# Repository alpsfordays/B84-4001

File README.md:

# B84-4001

The B84-4001 keyboard PCB is a replacement (rejuvenation? revival?) PCB that makes use of the G84-4001's layout, switches, and keycaps and puts them into a subjectively more usable form. It was originally created as a personal project to make use of a new-old-stock controller-less G84 module (a G84-4001QAU/00).

It supports one layout, the 83-key layout used by the aforementioned modules, though support for G84 variants with Windows keys may be added in future. No promises. It's all autorouted too, which may change as I work on this more.

I will gladly assist or give tips on assembly, firmware or use (you can find me on Discord as `bean#7178`), but please first read this README through.

This board is designed for Cherry ML switches in 18mm spacing, mounted directly onto the PCB; ML does not use a plate to hold the switches. The PCB has M2 mount holes along the perimeter, allowing one to make it into a sandwich case with another PCB as the backplate or mount into a custom case. This is **will not fit** in Cherry G84 keyboard cases - it is meant as a standalone keyboard.

I ordered revision zero with green soldermask, 0.8 millimetre with HASL. Revision one (what this repo is) has had its edges tidied up and excess silkscreen reference markings removed. When ordering, I highly recommend *not* specifying 0.8mm thickness - the stock PCB is 1.6mm so I recommend that.

### Controller and Firmware

This board uses an [RP2040 ItsyBitsy](https://www.adafruit.com/product/4888) from Adafruit as the keyboard controller, and the firmware is written in [KMK](https://github.com/KMKfw/kmk_firmware). It should be compatible with any other ItsyBitsy, including the 32u4 variant, but I've yet to try any of those and there may be some tweaks to KMK needed to support them (and of course for the 32u4, a port to TMK/QMK).

### Assembly

Here's the order of operations.

1.  Assemble your parts.
	* 83 Cherry ML switches
	* 83 1N4148 diodes, through-hole or SMD
	* 2.56mm headers
	* An RP2040 ItsyBitsy
	* Keycaps
	* Stabilizer inserts
	* (for sandwich casing) M2\*8 standoffs and M2\*3 screws, rubber feet and a second PCB

2.  Solder the diodes
	* Cathode to the square pads.
	* You will notice there are two sides to the PCB, a side **with** silkscreen and a side without. The side **with** silkscreen is the side from which you will insert or place the diodes - although the pads are also on the other, silkscreen-less side, do not put the diodes on that side unless you wish to have your keycaps bottom out 2 millimetres early.
	* 
	* Once the diodes are soldered, use a pair of flush-cutters to clip the diode legs as close to the PCB as possible, again because of keycap clearance. Note in the image above that when viewing the PCB from the silkscreen-less side; there should be no diodes visible and the legs should be cut flush or as close to flush as possible. 

3.  Solder the headers.
	* Solder the headers, again on the silkscreen side. Clip the headers to be flush or as close to flush as possible on the silkscreen-less side.

4.  Solder the adorably small switches.
	* Now take your ML switches and solder them in - insert them from the silkscreen-less side and get to work melting metal onto those pins. 

5.  Solder the ItsyBitsy.
	* Test that KMK works on the ItsyBitsy, then solder it in as well, component-side facing away from the PCB.

> For sandwich casing, install the standoffs and screw it all together using the second PCB as a backplate. Install rubber feet as desired.

6.  Test and use.
	* Make sure the keys work correctly and all register. Customize the firmware to suit your needs, though of course note that the matrix's representation in the firmware is reversed because... things (I'm lazy). That it works is what matters to me.
	* Install the stabilizer inserts and keycaps (and a touch of lube on the stabilizer wires to taste).

### Licenses

All software in this repository is licensed under the [GNU Public License,
version 3](https://www.gnu.org/licenses/gpl-3.0-standalone.html).
All hardware designs and documentation is licensed under the [Creative Commons
Attribution-NonCommercial-ShareAlike 4.0](https://creativecommons.org/licenses/by-nc-sa/4.0/)
license.

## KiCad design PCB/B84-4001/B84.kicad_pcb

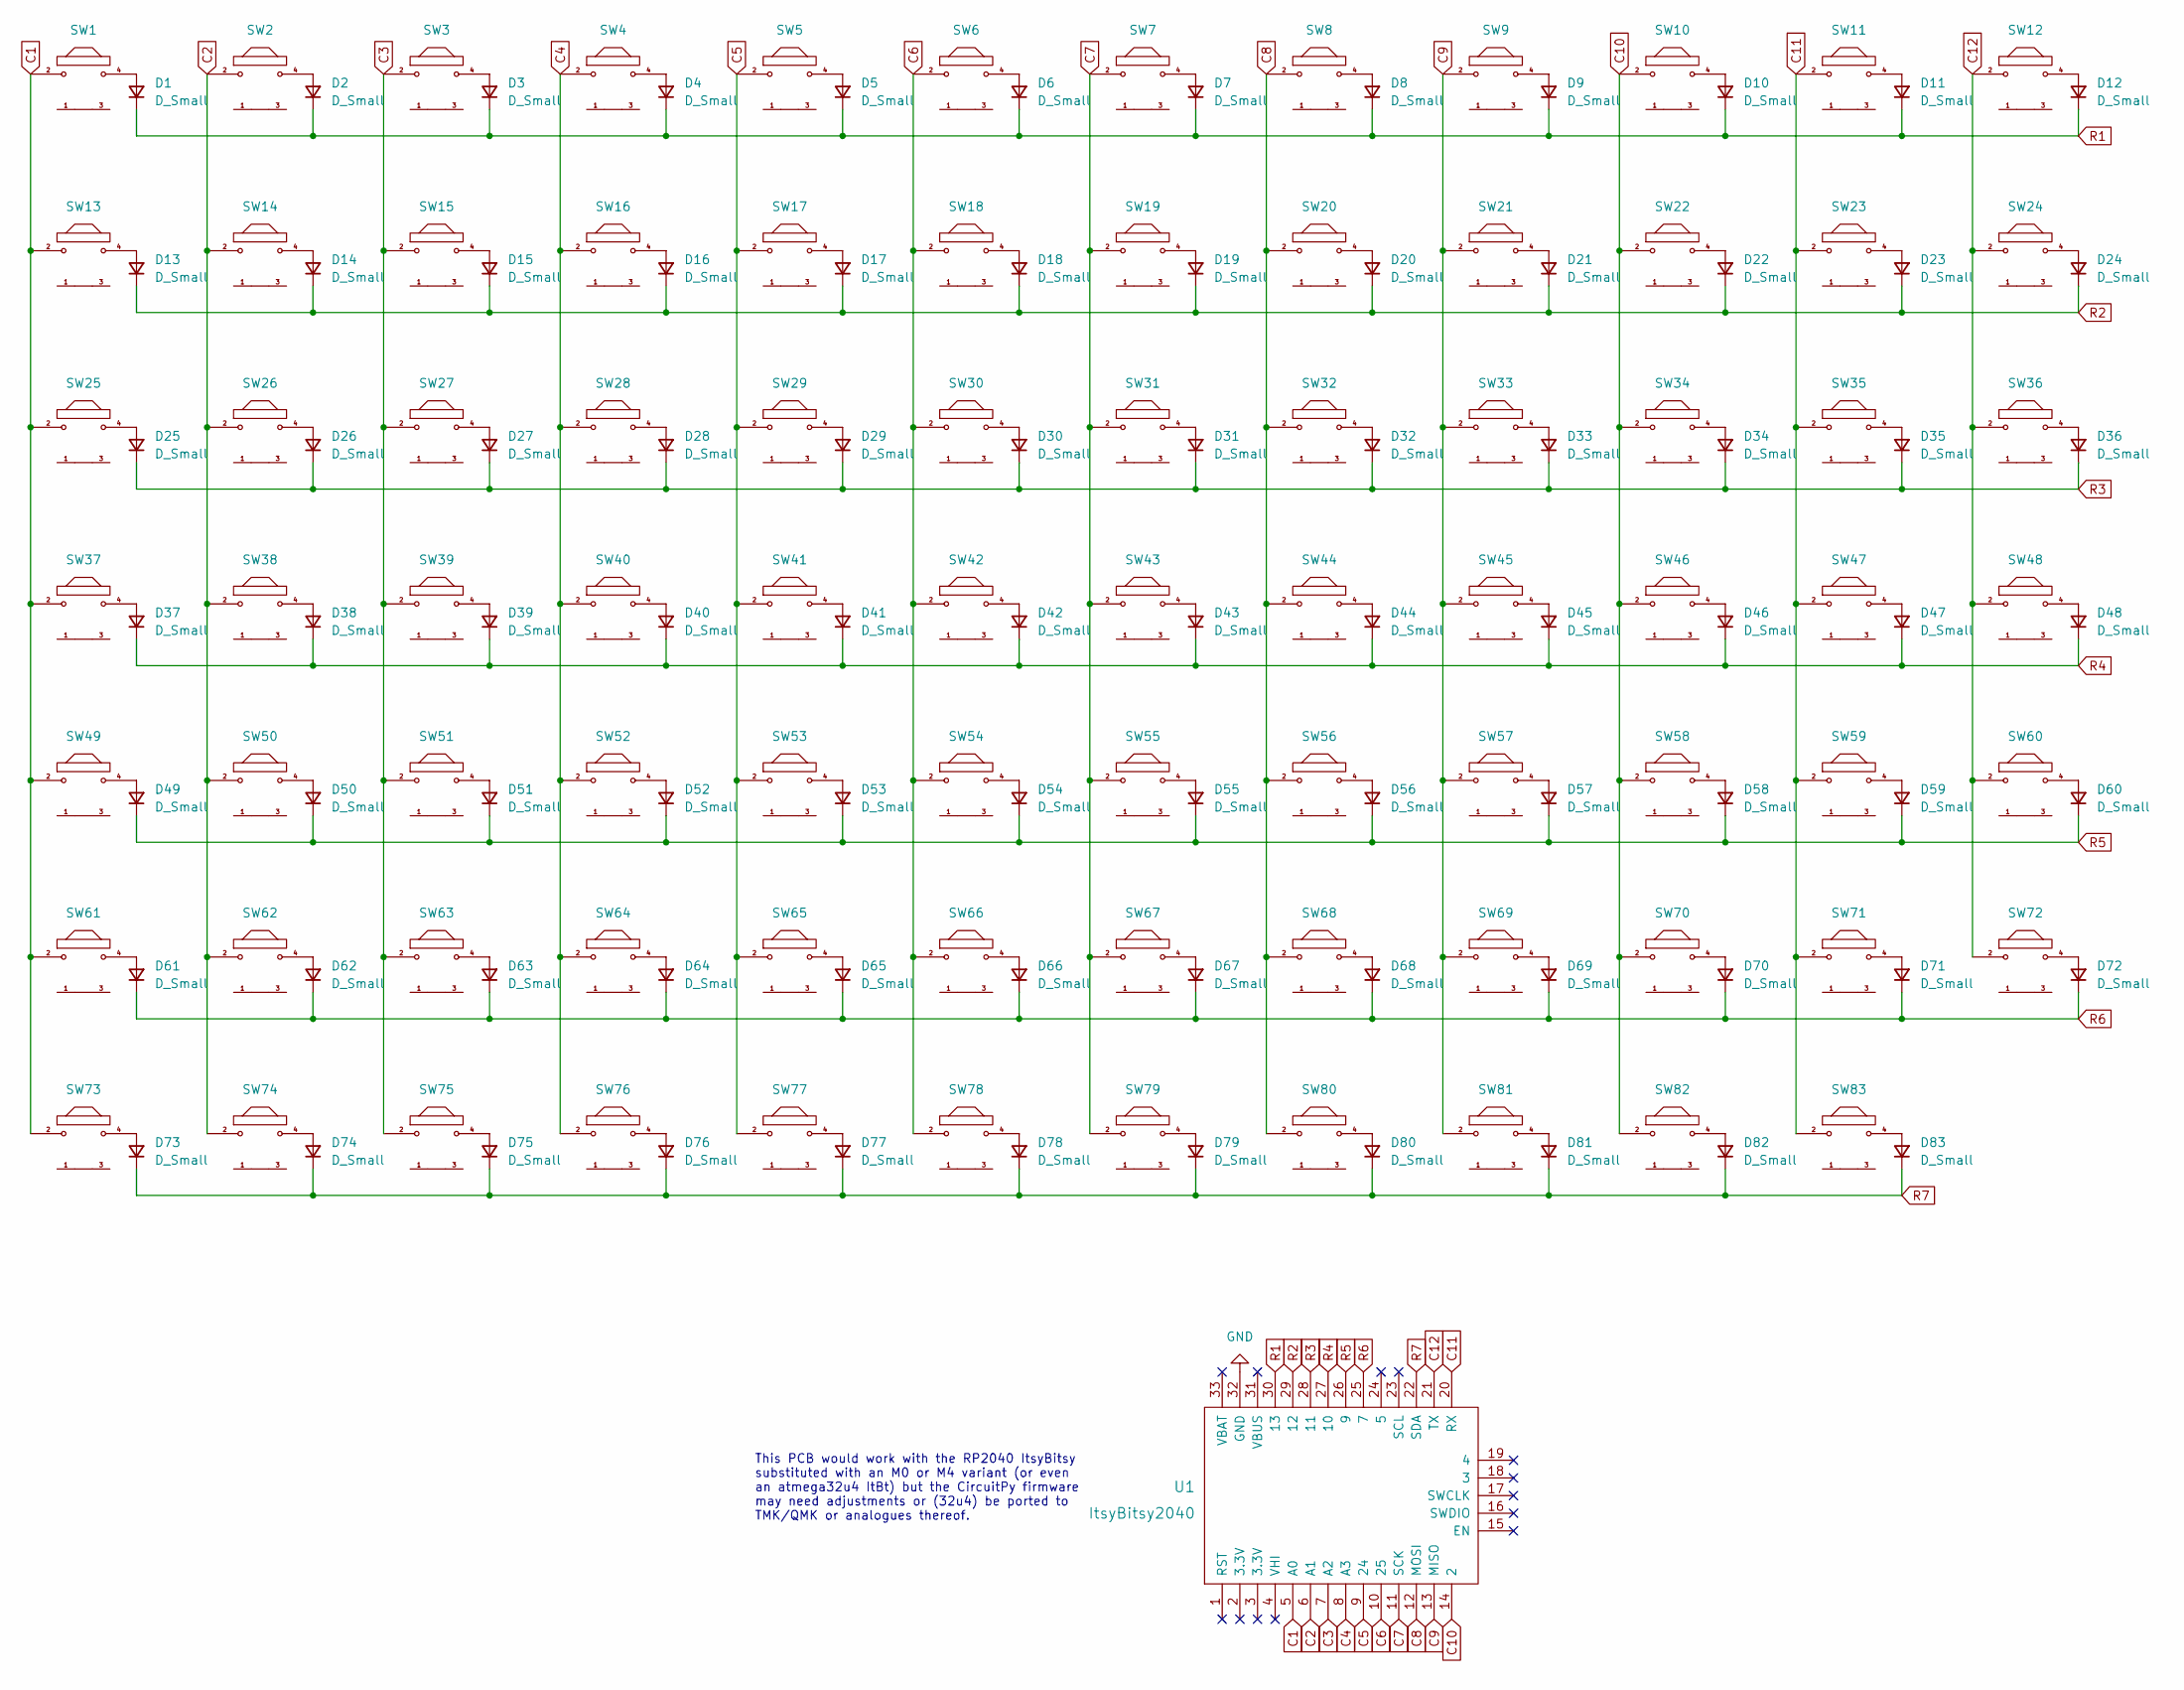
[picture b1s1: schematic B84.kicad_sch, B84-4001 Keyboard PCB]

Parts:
D1, D2, D3, D4, D5, D6, D7, D8, D9, D10, D11, D12, D13, D14, D15, D16, D17, D18, D19, D20, D21, D22, D23, D24, D25, D26, D27, D28, D29, D30, D31, D32, D33, D34, D35, D36, D37, D38, D39, D40, D41, D42, D43, D44, D45, D46, D47, D48, D49, D50, D51, D52, D53, D54, D55, D56, D57, D58, D59, D60, D61, D62, D63, D64, D65, D66, D67, D68, D69, D70, D71, D72, D73, D74, D75, D76, D77, D78, D79, D80, D81, D82, D83: D_Small
SW1, SW2, SW3, SW4, SW5, SW6, SW7, SW8, SW9, SW10, SW11, SW12, SW13, SW14, SW15, SW16, SW17, SW18, SW19, SW20, SW21, SW22, SW23, SW24, SW25, SW26, SW27, SW28, SW29, SW30, SW31, SW32, SW33, SW34, SW35, SW36, SW37, SW38, SW39, SW40, SW41, SW42, SW43, SW44, SW45, SW46, SW47, SW48, SW49, SW50, SW51, SW52, SW53, SW54, SW55, SW56, SW57, SW58, SW59, SW60, SW61, SW62, SW63, SW64, SW65, SW66, SW67, SW68, SW69, SW70, SW71, SW72, SW73, SW74, SW75, SW76, SW77, SW78, SW79, SW80, SW81, SW82, SW83: ML
U1: ItsyBitsy2040; ibrp2040_custom

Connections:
C1: SW1.2, SW13.2, SW25.2, SW37.2, SW49.2, SW61.2, SW73.2, U1.5 (A0)
C2: SW2.2, SW14.2, SW26.2, SW38.2, SW50.2, SW62.2, SW74.2, U1.6 (A1)
C3: SW3.2, SW15.2, SW27.2, SW39.2, SW51.2, SW63.2, SW75.2, U1.7 (A2)
C4: SW4.2, SW16.2, SW28.2, SW40.2, SW52.2, SW64.2, SW76.2, U1.8 (A3)
C5: SW5.2, SW17.2, SW29.2, SW41.2, SW53.2, SW65.2, SW77.2, U1.9 (24)
C6: SW6.2, SW18.2, SW30.2, SW42.2, SW54.2, SW66.2, SW78.2, U1.10 (25)
C7: SW7.2, SW19.2, SW31.2, SW43.2, SW55.2, SW67.2, SW79.2, U1.11 (SCK)
C8: SW8.2, SW20.2, SW32.2, SW44.2, SW56.2, SW68.2, SW80.2, U1.12 (MOSI)
C9: SW9.2, SW21.2, SW33.2, SW45.2, SW57.2, SW69.2, SW81.2, U1.13 (MISO)
C10: SW10.2, SW22.2, SW34.2, SW46.2, SW58.2, SW70.2, SW82.2, U1.14 (2)
C11: SW11.2, SW23.2, SW35.2, SW47.2, SW59.2, SW71.2, SW83.2, U1.20 (RX)
C12: SW12.2, SW24.2, SW36.2, SW48.2, SW60.2, SW72.2, U1.21 (TX)
GND: U1.32 (GND)
unnamed: D1.2 (A), SW1.4
unnamed: D2.2 (A), SW2.4
unnamed: D3.2 (A), SW3.4
unnamed: D4.2 (A), SW4.4
unnamed: D5.2 (A), SW5.4
unnamed: D6.2 (A), SW6.4
unnamed: D7.2 (A), SW7.4
unnamed: D8.2 (A), SW8.4
unnamed: D9.2 (A), SW9.4
unnamed: D10.2 (A), SW10.4
unnamed: D11.2 (A), SW11.4
unnamed: D12.2 (A), SW12.4
unnamed: D13.2 (A), SW13.4
unnamed: D14.2 (A), SW14.4
unnamed: D15.2 (A), SW15.4
unnamed: D16.2 (A), SW16.4
unnamed: D17.2 (A), SW17.4
unnamed: D18.2 (A), SW18.4
unnamed: D19.2 (A), SW19.4
unnamed: D20.2 (A), SW20.4
unnamed: D21.2 (A), SW21.4
unnamed: D22.2 (A), SW22.4
unnamed: D23.2 (A), SW23.4
unnamed: D24.2 (A), SW24.4
unnamed: D25.2 (A), SW25.4
unnamed: D26.2 (A), SW26.4
unnamed: D27.2 (A), SW27.4
unnamed: D28.2 (A), SW28.4
unnamed: D29.2 (A), SW29.4
unnamed: D30.2 (A), SW30.4
unnamed: D31.2 (A), SW31.4
unnamed: D32.2 (A), SW32.4
unnamed: D33.2 (A), SW33.4
unnamed: D34.2 (A), SW34.4
unnamed: D35.2 (A), SW35.4
unnamed: D36.2 (A), SW36.4
unnamed: D37.2 (A), SW37.4
unnamed: D38.2 (A), SW38.4
unnamed: D39.2 (A), SW39.4
unnamed: D40.2 (A), SW40.4
unnamed: D41.2 (A), SW41.4
unnamed: D42.2 (A), SW42.4
unnamed: D43.2 (A), SW43.4
unnamed: D44.2 (A), SW44.4
unnamed: D45.2 (A), SW45.4
unnamed: D46.2 (A), SW46.4
unnamed: D47.2 (A), SW47.4
unnamed: D48.2 (A), SW48.4
unnamed: D49.2 (A), SW49.4
unnamed: D50.2 (A), SW50.4
unnamed: D51.2 (A), SW51.4
unnamed: D52.2 (A), SW52.4
unnamed: D53.2 (A), SW53.4
unnamed: D54.2 (A), SW54.4
unnamed: D55.2 (A), SW55.4
unnamed: D56.2 (A), SW56.4
unnamed: D57.2 (A), SW57.4
unnamed: D58.2 (A), SW58.4
unnamed: D59.2 (A), SW59.4
unnamed: D60.2 (A), SW60.4
unnamed: D61.2 (A), SW61.4
unnamed: D62.2 (A), SW62.4
unnamed: D63.2 (A), SW63.4
unnamed: D64.2 (A), SW64.4
unnamed: D65.2 (A), SW65.4
unnamed: D66.2 (A), SW66.4
unnamed: D67.2 (A), SW67.4
unnamed: D68.2 (A), SW68.4
unnamed: D69.2 (A), SW69.4
unnamed: D70.2 (A), SW70.4
unnamed: D71.2 (A), SW71.4
unnamed: D72.2 (A), SW72.4
unnamed: D73.2 (A), SW73.4
unnamed: D74.2 (A), SW74.4
unnamed: D75.2 (A), SW75.4
unnamed: D76.2 (A), SW76.4
unnamed: D77.2 (A), SW77.4
unnamed: D78.2 (A), SW78.4
unnamed: D79.2 (A), SW79.4
unnamed: D80.2 (A), SW80.4
unnamed: D81.2 (A), SW81.4
unnamed: D82.2 (A), SW82.4
unnamed: D83.2 (A), SW83.4
R1: D1.1 (K), D2.1 (K), D3.1 (K), D4.1 (K), D5.1 (K), D6.1 (K), D7.1 (K), D8.1 (K), D9.1 (K), D10.1 (K), D11.1 (K), D12.1 (K), U1.30 (13)
R2: D13.1 (K), D14.1 (K), D15.1 (K), D16.1 (K), D17.1 (K), D18.1 (K), D19.1 (K), D20.1 (K), D21.1 (K), D22.1 (K), D23.1 (K), D24.1 (K), U1.29 (12)
R3: D25.1 (K), D26.1 (K), D27.1 (K), D28.1 (K), D29.1 (K), D30.1 (K), D31.1 (K), D32.1 (K), D33.1 (K), D34.1 (K), D35.1 (K), D36.1 (K), U1.28 (11)
R4: D37.1 (K), D38.1 (K), D39.1 (K), D40.1 (K), D41.1 (K), D42.1 (K), D43.1 (K), D44.1 (K), D45.1 (K), D46.1 (K), D47.1 (K), D48.1 (K), U1.27 (10)
R5: D49.1 (K), D50.1 (K), D51.1 (K), D52.1 (K), D53.1 (K), D54.1 (K), D55.1 (K), D56.1 (K), D57.1 (K), D58.1 (K), D59.1 (K), D60.1 (K), U1.26 (9)
R6: D61.1 (K), D62.1 (K), D63.1 (K), D64.1 (K), D65.1 (K), D66.1 (K), D67.1 (K), D68.1 (K), D69.1 (K), D70.1 (K), D71.1 (K), D72.1 (K), U1.25 (7)
R7: D73.1 (K), D74.1 (K), D75.1 (K), D76.1 (K), D77.1 (K), D78.1 (K), D79.1 (K), D80.1 (K), D81.1 (K), D82.1 (K), D83.1 (K), U1.22 (SDA)

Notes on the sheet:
This PCB would work with the RP2040 ItsyBitsy substituted with an M0 or M4 variant (or even an atmega32u4 ItBt) but the CircuitPy firmware may need adjustments or (32u4) be ported to TMK/QMK or analogues thereof.

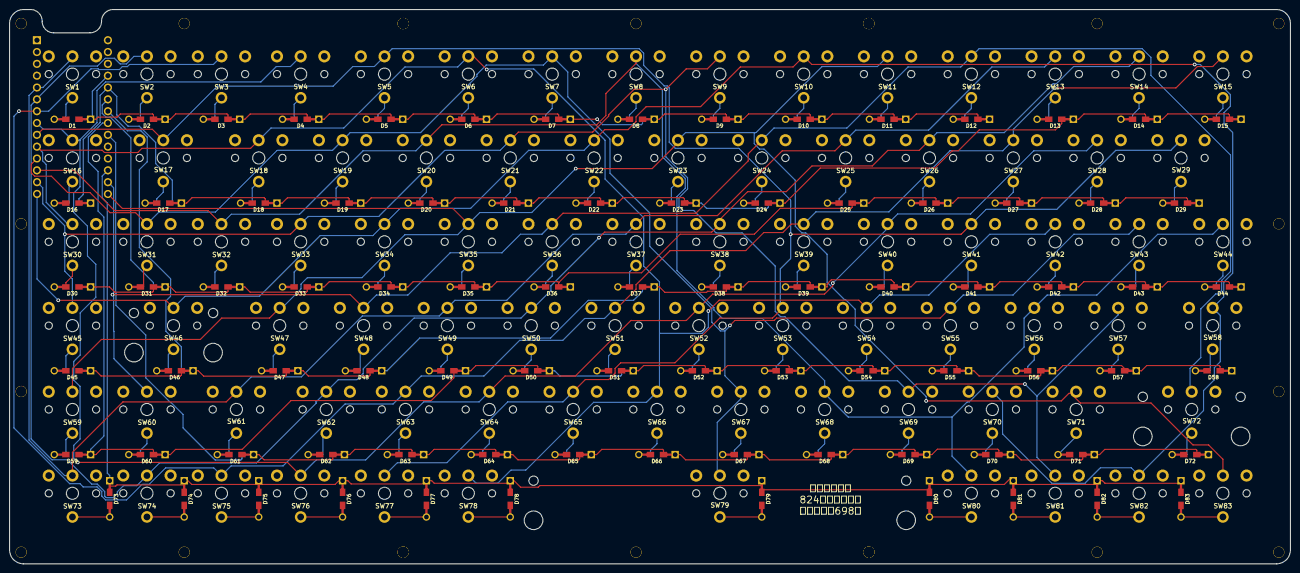
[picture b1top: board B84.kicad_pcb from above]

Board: 2 copper layers, 275.0 x 119.0 mm, 185 parts (0 on the bottom side), 102 nets.

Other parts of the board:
J1, J2, J3, J4, J5, J6, J7, J9, J10, J11, J12, J13, J14, J15, J16, J17, J18, J19: D2; SinglePad

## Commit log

2022-05-31 Corrected references, added .pretty library
    Original files referenced the custom ML footprints I made in a much larger library, so I put them into their own library and corrected the files' references.

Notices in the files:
PCB/B84-4001/B84.kicad_pcb:
Licensed under CC BY-NA-SA 4.0
